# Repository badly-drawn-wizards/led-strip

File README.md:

# Description #
This is a Ethernet controlled RGB led-strip music visualizer. It uses WS2812
strip for display, a PIC16F1825 as a host controller and a ENC28J60 for ethernet
communication. The communication is one-way with raw ethernet frames (Yay! It's terrible). This
project has three parts

- Host controller code in __micro__
- A __daemon__ to listen to a pulseaudio monitor and send the visualization to the led-strip device with a hard-coded MAC address.
- A _completely untested_ __board__ design for the device. I'll return to it someday. Maybe.

# Demo #
[In this YouTube video](https://youtu.be/0CW2xSNjpUU) is a demonstration of a breadboard prototype.

# Disclaimer #
This project is entirely for my own satisfaction and not left in a complete, nor readily consumable state.

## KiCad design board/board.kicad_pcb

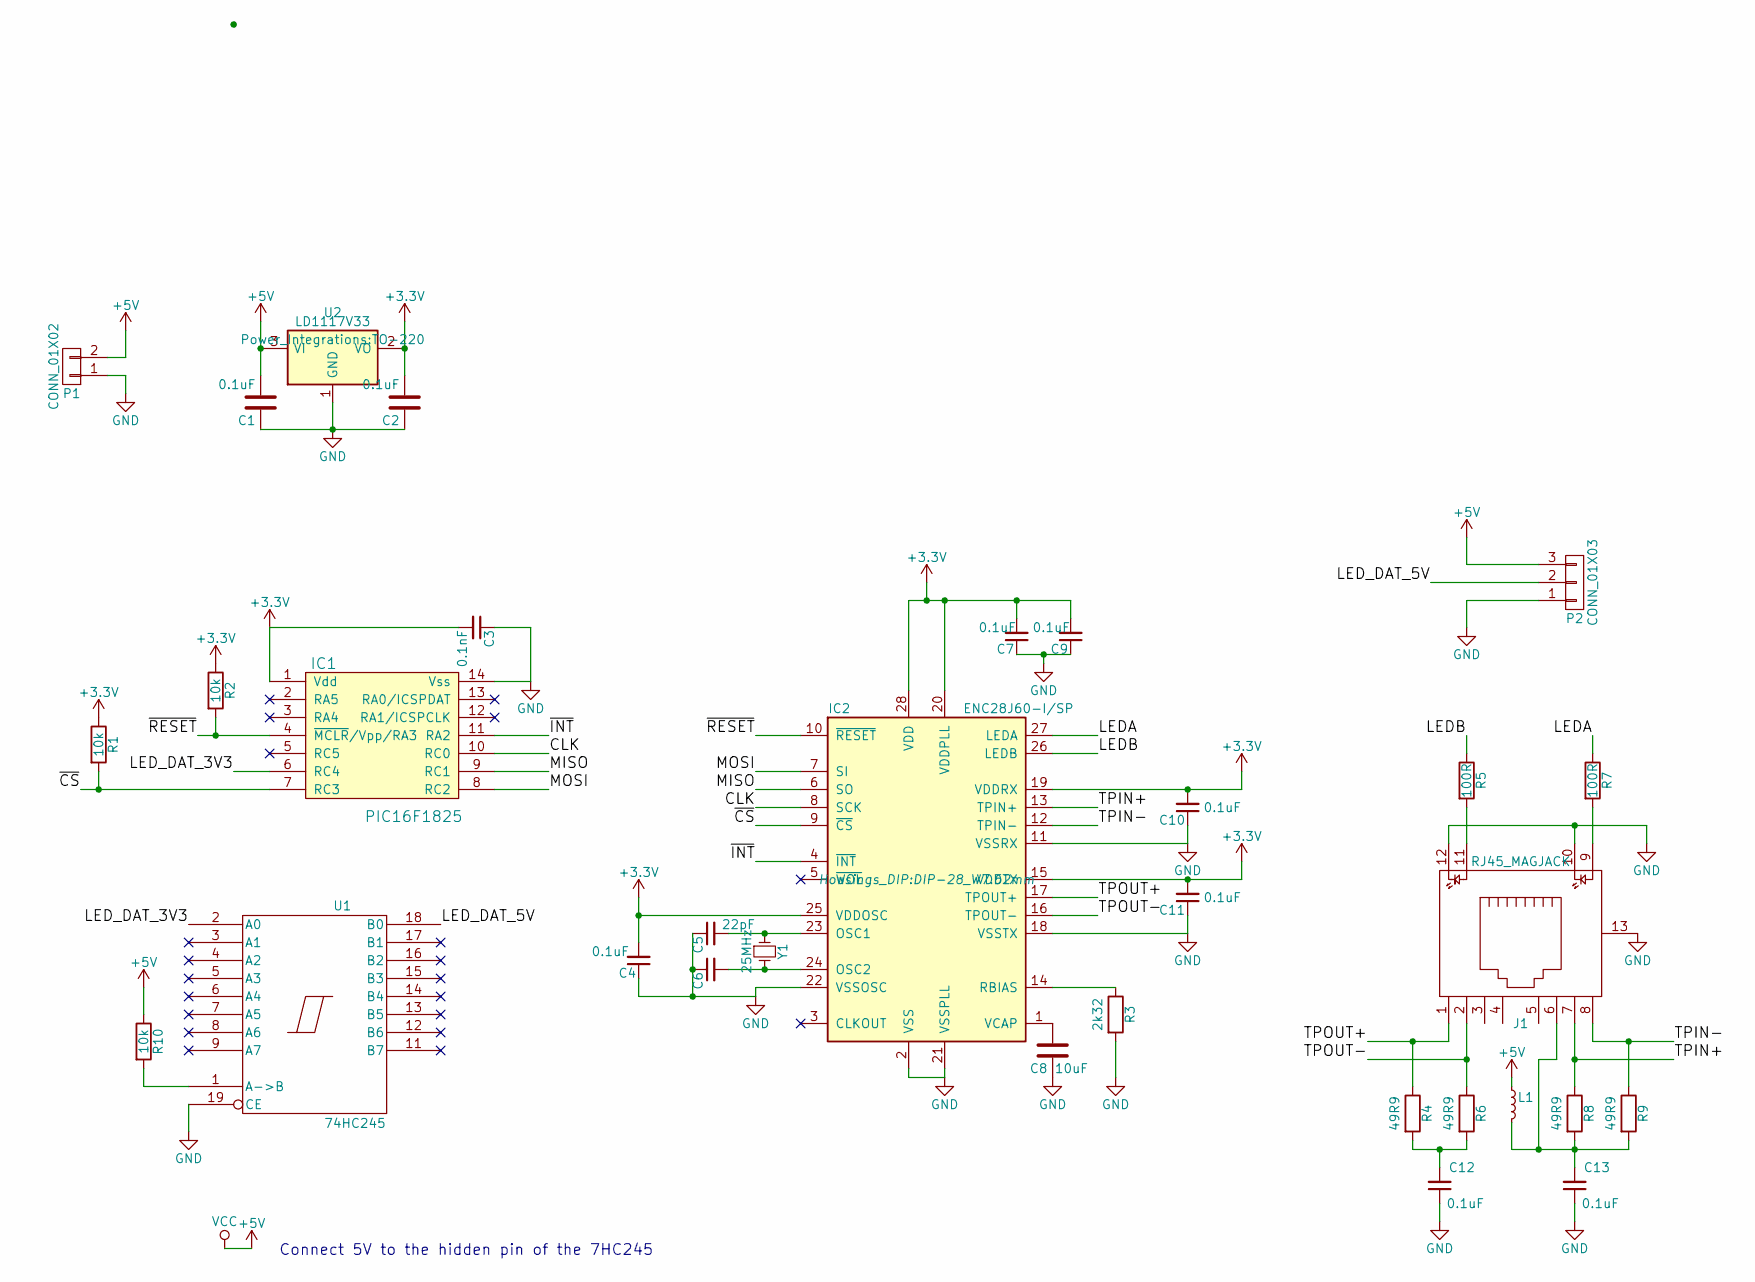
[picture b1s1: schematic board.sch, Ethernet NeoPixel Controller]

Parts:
C1, C2, C4, C7, C9, C10, C11, C12, C13: 0.1uF; C_Disc_D3_P2.5
C3: 0.1nF; C_Disc_D3_P2.5
C5, C6: 22pF; C_Disc_D3_P2.5
C8: 10uF; C_Radial_D5_L6_P2.5
IC1: PIC16F1825; DIP-14_W7.62mm
IC2: ENC28J60-I/SP; DIP-28_W7.62mm
J1: RJ45_MAGJACK
L1: L_Small; Choke_Horizontal_RM10mm
P1: CONN_01X02; Pin_Header_Straight_1x02
P2: CONN_01X03; Pin_Header_Straight_1x03
R1, R2, R10: 10k; Resistor_Horizontal_RM10mm
R3: 2k32; Resistor_Horizontal_RM10mm
R4, R6, R8, R9: 49R9; Resistor_Horizontal_RM10mm
R5, R7: 100R; Resistor_Horizontal_RM10mm
U1: 74HC245; DIP-20_W7.62mm
U2: LD1117V33; TO-220
Y1: 25MHz; Crystal_HC49-U_Vertical

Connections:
+3V3: C2.2, C3.2, C4.2, C7.2, C9.2, C10.2, C11.2, IC1.1 (Vdd), IC2.15 (VDDTX), IC2.19 (VDDRX), IC2.20 (VDDPLL), IC2.25 (VDDOSC), IC2.28 (VDD), R1.1, R2.1, U2.2 (VO)
+5V: C1.2, L1.1, P1.2, P2.3, R10.1, U1.20 (VCC), U2.3 (VI)
/CLK: IC1.10 (RC0), IC2.8 (SCK)
/LEDA: IC2.27 (LEDA), R7.1
/LEDB: IC2.26 (LEDB), R5.1
/LED_DAT_3V3: IC1.6 (RC4), U1.2 (A0)
/LED_DAT_5V: P2.2, U1.18 (B0)
/MISO: IC1.9 (RC1), IC2.6 (SO)
/MOSI: IC1.8 (RC2), IC2.7 (SI)
/TPIN+: IC2.13 (TPIN+), J1.7, R8.1
/TPIN-: IC2.12 (TPIN-), J1.8, R9.1
/TPOUT+: IC2.17 (TPOUT+), J1.1, R4.1
/TPOUT-: IC2.16 (TPOUT-), J1.2, R6.1
/~CS~: IC1.7 (RC3), IC2.9 (~CS), R1.2
/~INT~: IC1.11 (RA2), IC2.4 (~INT)
/~RESET~: IC1.4 (~MCLR~/Vpp/RA3), IC2.10 (~RESET), R2.2
GND: C1.1, C2.1, C3.1, C4.1, C5.1, C6.1, C7.1, C8.1, C9.1, C10.1, C11.1, C12.1, C13.1, IC1.14 (Vss), IC2.2 (VSS), IC2.11 (VSSRX), IC2.18 (VSSTX), IC2.21 (VSSPLL), IC2.22 (VSSOSC), J1.10, J1.12, J1.13, P1.1, P2.1, R3.2, U1.10 (GND), U1.19 (CE), U2.1 (GND)
unnamed: C5.2, IC2.23 (OSC1), Y1.1
unnamed: C6.2, IC2.24 (OSC2), Y1.2
unnamed: C8.2, IC2.1 (VCAP)
unnamed: C12.2, R4.2, R6.2
unnamed: C13.2, J1.6, L1.2, R8.2, R9.2
unnamed: IC2.14 (RBIAS), R3.1
unnamed: J1.9, R7.2
unnamed: J1.11, R5.2
unnamed: R10.2, U1.1 (A->B)

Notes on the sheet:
Connect 5V to the hidden pin of the 7HC245

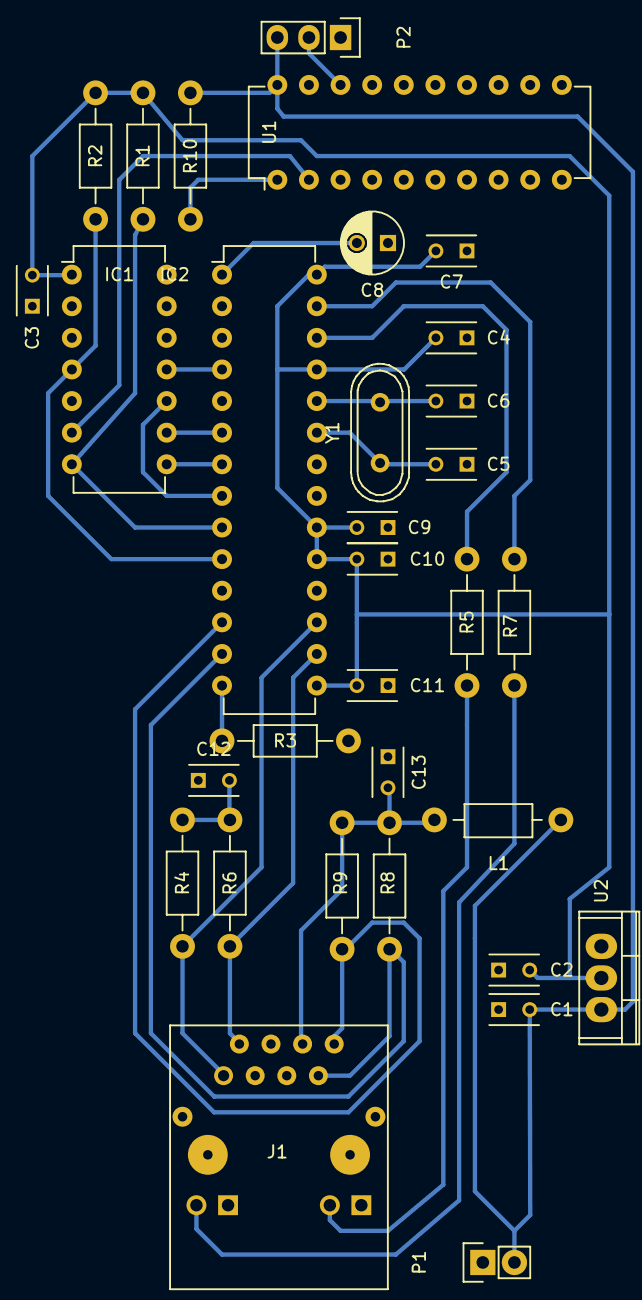
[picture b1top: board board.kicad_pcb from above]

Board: 2 copper layers, 32 parts (0 on the bottom side), 26 nets.

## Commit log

2016-09-24 Demo of WS2812 strip
2016-09-29 I present this mantra in lieu of good practice:
    Commit often, commit early
2016-09-29 Begin PulseAudio daemon
2016-09-29 Version .dir-locals.el
2016-09-29 Add .gitignore
2016-09-30 Fixed SPI by clearing ANSELC on all SPI pins.
2016-10-01 Initial schematic design
2016-10-03 Finished PCB
2016-10-03 Initial work to send raw ethernet frames.
2016-10-03 Add Makefile for daemon
2016-10-03 Add .dir-locals.el for daemon.
2016-10-03 Set LED_PIN correctly
2016-10-03 Remove testing code from main loop
2016-10-03 Extract function for led initialization
2016-10-03 Group interrupt related code together
2016-10-03 Fixed incorrect offset to packet length.
2016-10-03 Fix potential buffer over-read
2016-10-03 Added slightly more instructive comment
2016-12-26 Rest of the owl (micro edition).
2016-12-26 Rest of the owl (daemon edition)
2016-12-26 Rest of the owl (board edition)
2016-12-26 Add README
2016-12-26 Be consistent with emphasis in README
